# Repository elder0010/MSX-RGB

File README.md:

# TMS9929A / TMS9928A RGB
## A RGB demodulator for TMS9929A / TMS9928A chip, mostly used on MSX computers and Colecovision. 

This board outputs RGB+CSYNC from the original YPbPr chip channels of the TMS99 chip. 
Output from each color channel can be adjusted using a trimmer. 
Based on the [Universele interface RGB op MSX1 en SV.328](http://www.msxarchive.nl/pub/msx/mirrors/hanso/hwdoityourself/rgbmsx1.pdf). Mine fixes the emitter follower transistors of this version.
This repository contains the KiCad project and the Gerber files, the [PDF schematics](https://github.com/elder0010/msx_rgb/blob/main/TMS9929_RGB_Adapter.pdf) and the [BOM](https://github.com/elder0010/msx_rgb/blob/main/TMS9929_RGB_Adapter.csv) file.

## Features
- Each channel can be tuned
- Provides audio output pin
- Provides 5V output pin (if you want to use it with an RGB Scart cable for "modern" TVs)
- Fits into the MSX composite modulator slot
- Extremely cheap!

## Video

## Sample output (photo taken on BVM 20DU)

## Assembled PCB

## The PCB in a Phonola VG-8020

## How to assemble
- Y, Pb, Pr signals must be taken directly from the TMS chip (pin 35,36,38 on TMS9928A or TMS9929A)
- Audio is from pin 4 of the AY38910
- 5V pin is optional: wire it only if you need to connect the computer to a scart TV.
- Removing the original composite modulator (on MSX) is not mandatory but encouraged: unfortunately it creates noises also on the RGB interface. Keep in mind that removing the modulator will disable the composite video and the RF video out of the machine.
- On the Phonola VG8020 I removed the RF modulator to make room for a 8 pin mini din connector. I used the [8pin Mini DIN to EuroSCART PACKAPUNCH cable for RGB modified consoles](https://www.retrogamingcables.co.uk/atari/8PIN-MINI-DIN-TO-RGB-EUROSCART-TIM-WORTHINGTON-NES-RGB-ATARI-2600-HAS-SUPERGUN-Sega-Game-Gear-Philips-CDi-Colecovision-Intellivision-Panasonic-3DO). It's possible also to desolder the original composite out connector and use a 8 pin DIN connector to make it compatible with a Sega Genesis 1 SCART cable.

## External view of the mini din connector (RF modulator has been removed)

## Perks
This board provides an RGB output for the TMS9929A / TMS9928A chip.
Although it's impossible to have 100% correct colours, it's possible to obtain a palette very close to the correct one in this way:
- Set each RGB trimmer to 0
- Turn up a little the RED and GREEN potentiometer until something visible appears on screen
- Turn up the BLUE potentiometer until the background becomes blueish - keep in mind that the blue channel is the most problematic one because of the TMS99x non-standard design
- Execute the command color 1,1 to set the screen and the text to black
- Notice how the black is blueish, and turn down the BLUE potentiometer until the background becomes less blueish ;)
- Execute the command color 15,4 to restore the screen to the default colours
- Repeat until you get a satisfactory result
- adjust the GREEN and the RED potentiometer accordingly 

In this way the palette should be close to the original.

## Compatibility
This board has been tested with TMS9929A (PAL) chip and TMS9928A (NTSC).

- PCB shape is the same of [TMS9929A RGB and Component adapter](https://hackaday.io/project/13056-tms9929a-rgb-and-component-adapter)
- Special thanks to [iz8dwf](https://www.youtube.com/iz8dwf)

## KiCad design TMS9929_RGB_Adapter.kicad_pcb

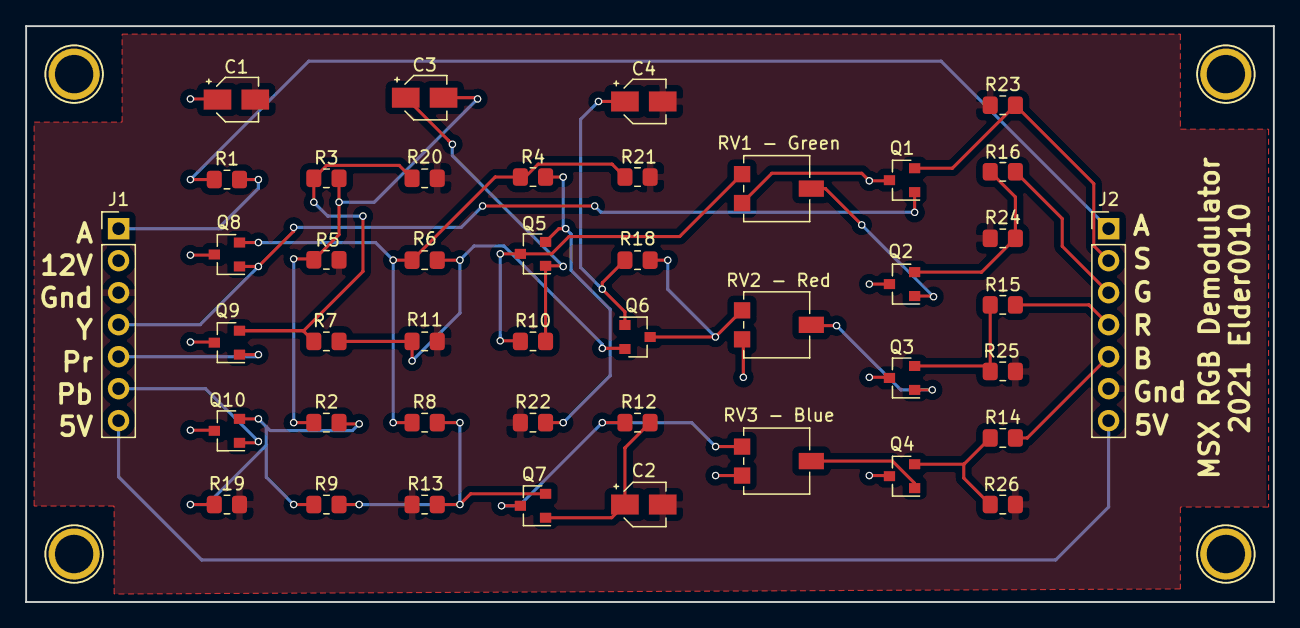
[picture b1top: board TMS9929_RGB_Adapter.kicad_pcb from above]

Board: 2 copper layers, 99.1 x 45.7 mm, 48 parts (0 on the bottom side), 31 nets.

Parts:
C1, C2, C3, C4: 16V/10UF; CP_Elec_3x5.3
J1, J2: Conn_01x07; PinHeader_1x07_P2.54mm_Vertical
P6, P7, P8, P9: CONN_01X01; 1pin
Q1, Q2, Q3, Q4, Q5, Q6, Q7, Q8, Q9, Q10: MMBT3904; SOT-23
R1: 2K2; R_0805_2012Metric_Pad1.20x1.40mm_HandSolder
R2, R3, R4, R5, R6, R7, R8, R9, R11, R13, R19, R20, R21, R22: 1K; R_0805_2012Metric_Pad1.20x1.40mm_HandSolder
R10, R12, R18: 100K; R_0805_2012Metric_Pad1.20x1.40mm_HandSolder
R14, R15, R16: 100R 1/4W; R_0805_2012Metric_Pad1.20x1.40mm_HandSolder
R23, R24, R25, R26: 4K7 1/4W; R_0805_2012Metric_Pad1.20x1.40mm_HandSolder
RV1 - Green, RV2 - Red, RV3 - Blue: 5K; Potentiometer_Vishay_TS53YL_Vertical

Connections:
GND: C1.2, C2.2, C4.2, J1.3, J2.6, R5.1, R11.1, R13.2, R19.2, R20.1, R21.1, R22.1, R23.1, R24.1, R25.1, R26.1
unnamed: C2.1, Q7.1, R12.1
unnamed: C3.1, Q5.1, R10.2
unnamed: C3.2, R2.1, R3.1, R5.2
unnamed: C4.1, Q6.1, R18.1
unnamed: J1.1, R1.2
unnamed: J1.4, Q1.1, Q8.1
unnamed: J1.5, Q9.1
unnamed: J1.6, Q10.1
unnamed: J1.7, J2.7
unnamed: J2.1, R1.1
unnamed: J2.2, Q1.2, R23.2
unnamed: J2.3, R16.1
unnamed: J2.4, R15.1
unnamed: J2.5, R14.1
unnamed: Q2.1, RV1 - Green.2
unnamed: Q2.2, R16.2, R24.2
unnamed: Q3.1, RV2 - Red.2
unnamed: Q3.2, R15.2, R25.2
unnamed: Q4.1, RV3 - Blue.2
unnamed: Q4.2, R14.2, R26.2
unnamed: Q5.2, R4.1, R22.2
unnamed: Q5.3, R10.1, RV1 - Green.3
unnamed: Q6.2, R6.1, R7.1, R11.2
unnamed: Q6.3, R18.2, RV2 - Red.3
unnamed: Q7.2, R8.1, R9.1, R13.1
unnamed: Q7.3, R12.2, RV3 - Blue.3
unnamed: Q8.2, R4.2, R6.2, R8.2, R21.2
unnamed: Q9.2, R3.2, R7.2, R20.2
unnamed: Q10.2, R2.2, R9.2, R19.1
VCC: C1.1, J1.2, Q1.3, Q2.3, Q3.3, Q4.3, Q8.3, Q9.3, Q10.3, RV1 - Green.1, RV2 - Red.1, RV3 - Blue.1

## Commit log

2021-12-25 first import
2021-12-25 added photos
2021-12-25 added image
2021-12-26 Removed useless lib
